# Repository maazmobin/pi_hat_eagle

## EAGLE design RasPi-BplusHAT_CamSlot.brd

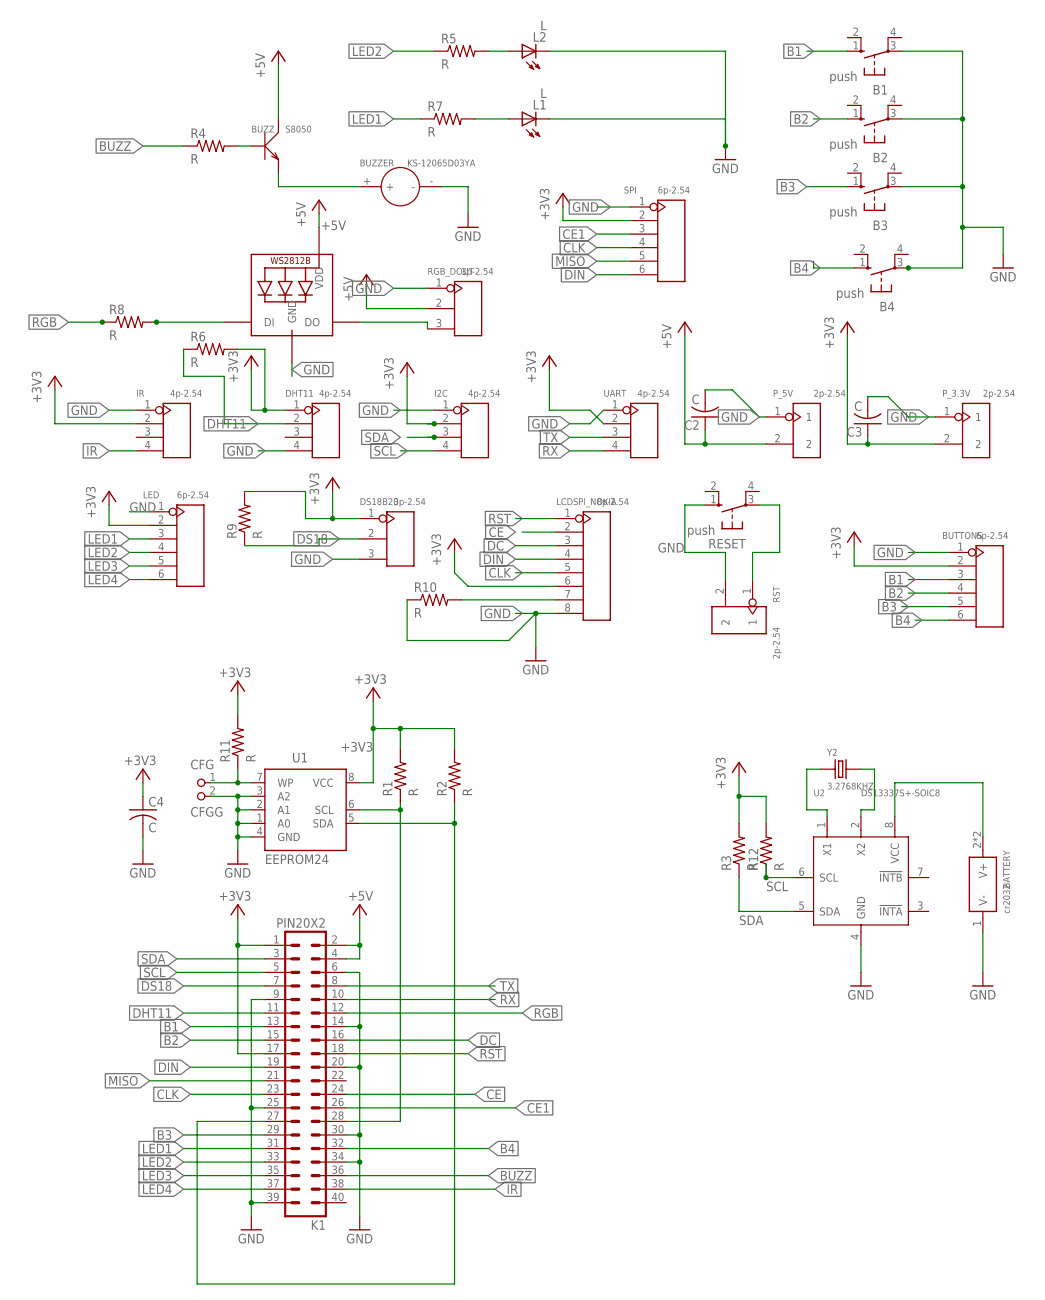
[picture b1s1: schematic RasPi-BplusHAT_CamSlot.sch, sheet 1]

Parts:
B1, B2, B3, B4: push; B3F-10XX
BATTERY: cr2032; BAT2P-20.32-CR2032
BUTTONS: 6p-2.54; H6-2.54
BUZZ: S8050; SOT-23
BUZZER: KS-12065D03YA; BZ2-7.6-D12.0XH6.5MM
C2, C3, C4: C; C1206
CFG: CFGG; PIN_W_2
DHT11: 4p-2.54; H4-2.54
DS18B20: 3p-2.54; H3-2.54
I2C: 4p-2.54; H4-2.54
IR: 4p-2.54; H4-2.54
K1: PIN20X2; PIN_20X2
L1, L2: L; LED5MM
LCDSPI_NOKIA: 8p-2.54; H8-2.54
LED: 6p-2.54; H6-2.54
P_3.3V, P_5V: 2p-2.54; H2-2.54
R1, R2, R3, R4, R5, R6, R7, R8, R9, R10, R11, R12: R; M1206
RESET: push; B3F-10XX
RGB1: WS2812B_5050N; WS2812B-NARROW
RGB_DOUT: 3p-2.54; H3-2.54
RST: 2p-2.54; H2-2.54
SPI: 6p-2.54; H6-2.54
U1: EEPROM24; SOIC8
U2: DS13337S+-SOIC8; SOIC8-1.27-5X4MM
UART: 4p-2.54; H4-2.54
Y2: 3.2768KHZ; X2-SMD-L2.0X1.2X0.55MM

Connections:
+3V3: BUTTONS.2, C3.1, C4.1, DHT11.1, DS18B20.1, I2C.2, IR.2, K1.1, K1.17, LCDSPI_NOKIA.6, LED.2, P_3.3V.2, R1.2, R2.2, R3.2, R6.2, R9.2, R11.2, R12.2, SPI.2, U1.8 (VCC), UART.2
+5V: BUZZ.3 (C), C2.1, K1.2, K1.4, P_5V.2, RGB1.1-VDD (VDD), RGB_DOUT.2
B1: B1.1 (S), BUTTONS.3, K1.13
B2: B2.1 (S), BUTTONS.4, K1.15
B3: B3.1 (S), BUTTONS.5, K1.29
B4: B4.1 (S), BUTTONS.6, K1.32
BUZZ: K1.36, R4.1
CE: K1.24, LCDSPI_NOKIA.2
CE1: K1.26, SPI.3
CLK: K1.23, LCDSPI_NOKIA.5, SPI.4
DC: K1.16, LCDSPI_NOKIA.3
DHT11: DHT11.2, K1.11, R6.1
DI: R8.2, RGB1.4-DIN (DI)
DIN: K1.19, LCDSPI_NOKIA.4, SPI.6
DS18: DS18B20.2, K1.7, R9.1
GND: B1.3, B2.3, B3.3, B4.3, BATTERY.1 (V-), BUTTONS.1, BUZZER.-, C2.2, C3.2, C4.2, CFG.2, DHT11.4, DS18B20.3, I2C.1, IR.1, K1.6, K1.9, K1.14, K1.20, K1.25, K1.30, K1.34, K1.39, L1.K (C), L2.K (C), LCDSPI_NOKIA.8, LED.1, P_3.3V.1, P_5V.1, R10.1, RESET.1 (S), RGB1.3-GND (GND), RGB_DOUT.1, RST.2, SPI.1, U1.1 (A0), U1.2 (A1), U1.3 (A2), U1.4 (GND), U2.4 (GND), UART.1
IR: IR.4, K1.38
LED1: K1.31, LED.3, R7.1
LED2: K1.33, LED.4, R5.1
LED3: K1.35, LED.5
LED4: K1.37, LED.6
MISO: K1.21, SPI.5
unnamed: K1.28, R1.1, U1.6 (SCL)
unnamed: K1.27, R2.1, U1.5 (SDA)
unnamed: CFG.1, R11.1, U1.7 (WP)
unnamed: BUZZ.2 (E), BUZZER.+
unnamed: L2.A, R5.2
unnamed: L1.A, R7.2
unnamed: RGB1.2-DOUT (DO), RGB_DOUT.3
unnamed: BATTERY.2 (V+), BATTERY.3 (V+), U2.8 (VCC)
unnamed: RESET.3, RST.1
unnamed: U2.1 (X1), Y2.1
unnamed: BUZZ.1 (B), R4.2
unnamed: U2.2 (X2), Y2.2
unnamed: LCDSPI_NOKIA.7, R10.2
RGB: K1.12, R8.1
RST: K1.18, LCDSPI_NOKIA.1
RX: K1.10, UART.4
SCL: I2C.4, K1.5, R12.1, U2.6 (SCL)
SDA: I2C.3, K1.3, R3.1, U2.5 (SDA)
TX: K1.8, UART.3

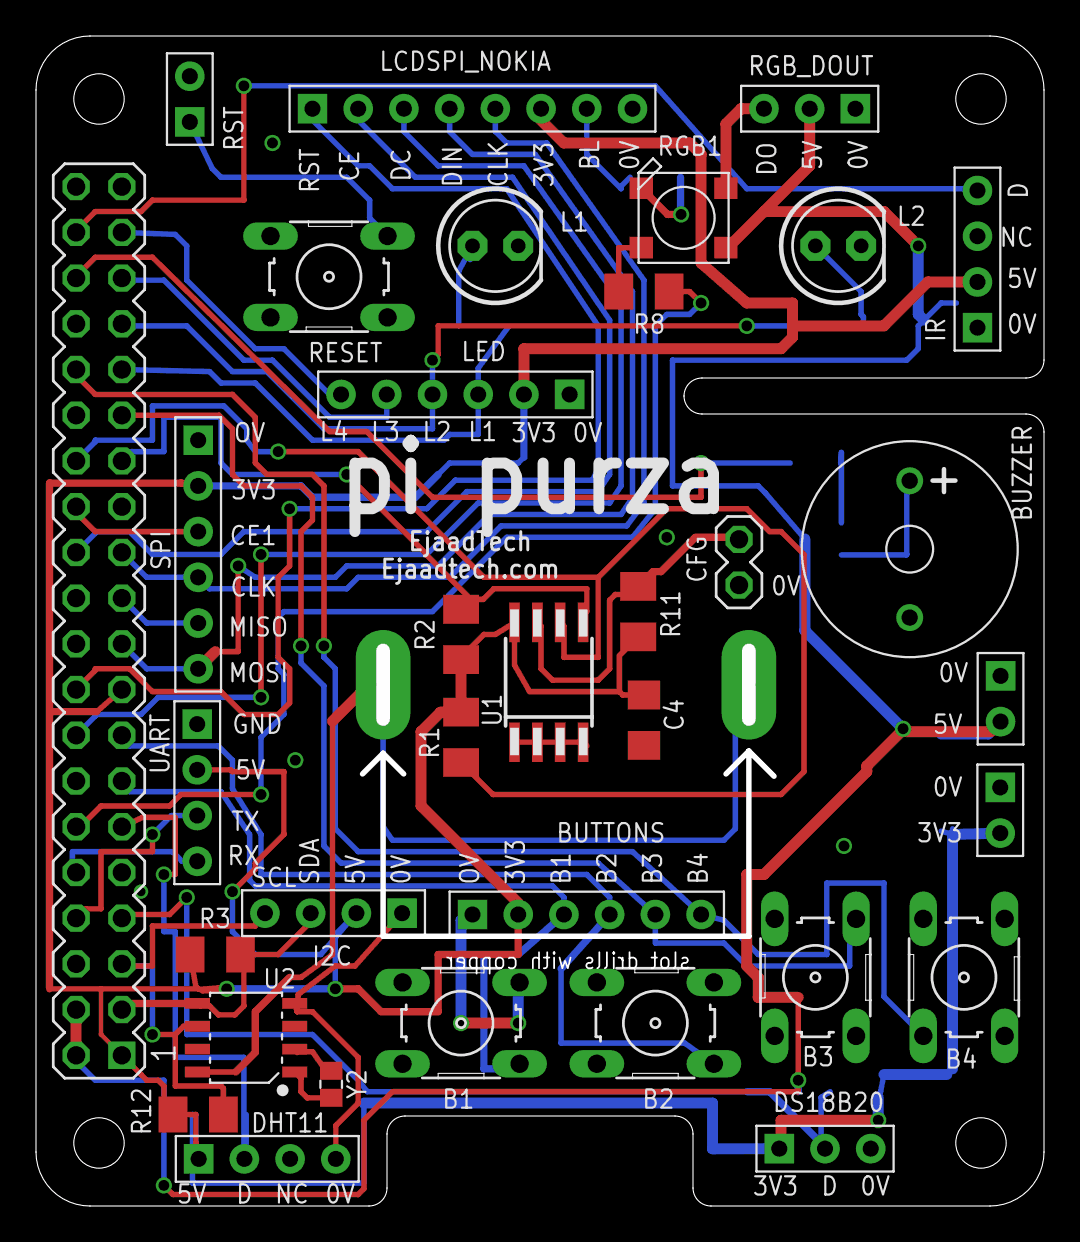
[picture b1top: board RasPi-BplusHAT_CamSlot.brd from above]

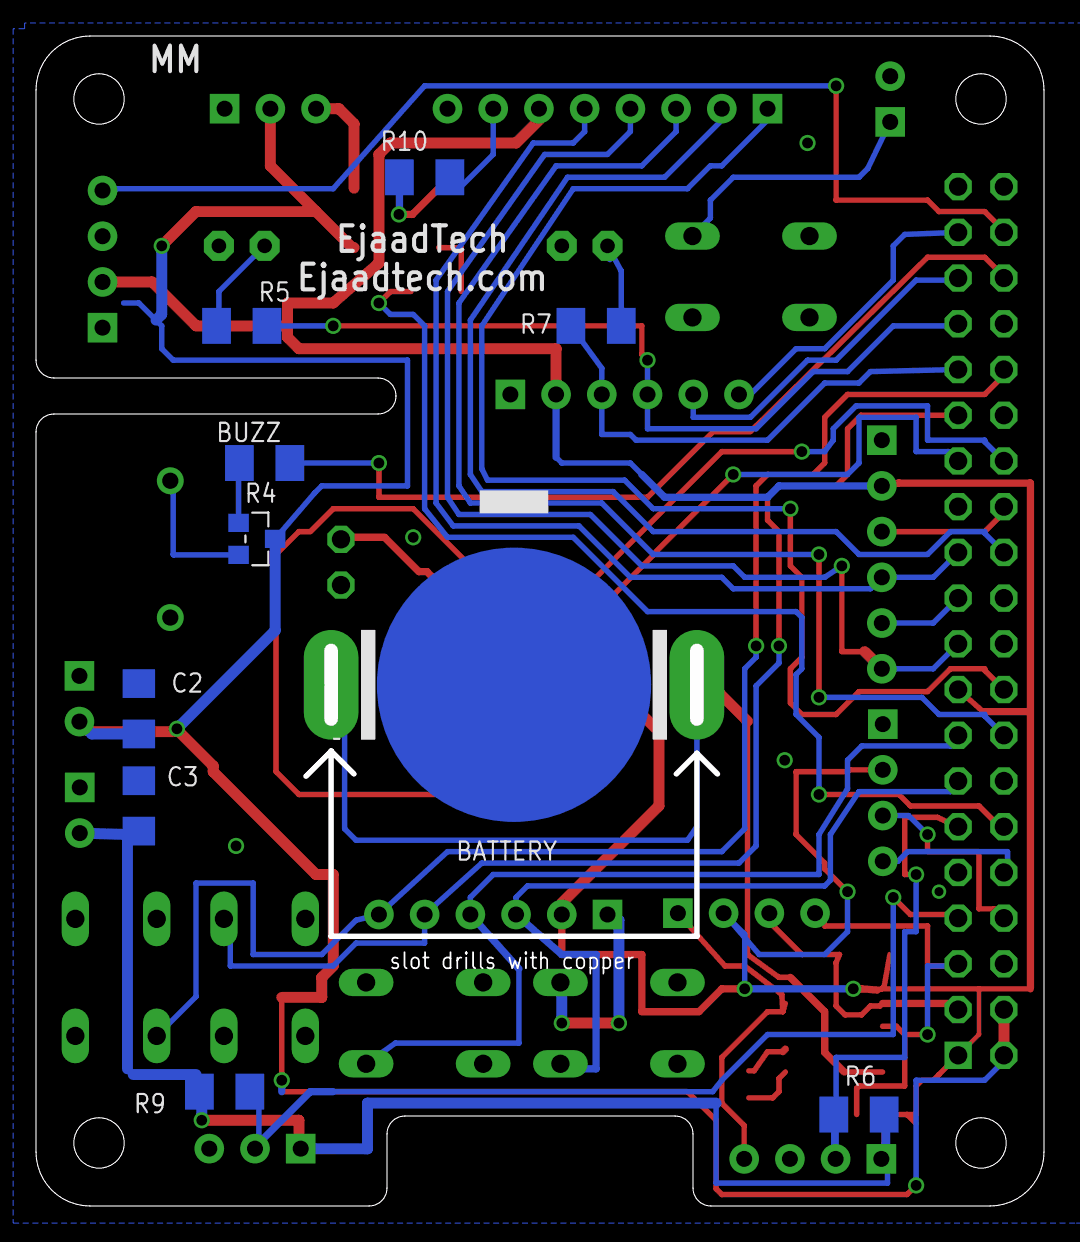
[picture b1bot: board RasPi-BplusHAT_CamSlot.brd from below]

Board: 2 copper layers, 56.0 x 65.0 mm, 44 parts (10 on the bottom side), 41 nets.

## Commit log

2016-06-10 :octocat: Added .gitattributes & .gitignore files
2016-06-10 Eagle schematic for custom pi hat
2016-06-13 update board and schmatic
2016-06-14 complete schematic 1
2016-06-15 before Re-PLACEMENT of parts by ZP
2016-06-15 routing completed
2016-06-15 DRC Clearance issues FIXED
2016-06-15 route completed, dht11 pullup res added
2016-06-16 pi hat update. layout complete.
    pull up complete
2016-06-18 on completion
2016-06-18 Completed Reviewing , MB
2016-06-21 pi hat completed. schemated edit. ( pi purza )
2016-06-27 little cosmetic edits in board file
2016-06-27 More cosmetics on the PCB

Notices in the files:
parts and their libraries:
SparkFun-Aesthetics: Licensing: Creative Commons ShareAlike 4.0 International - https://creativecommons.org/licenses/by-sa/4.0
